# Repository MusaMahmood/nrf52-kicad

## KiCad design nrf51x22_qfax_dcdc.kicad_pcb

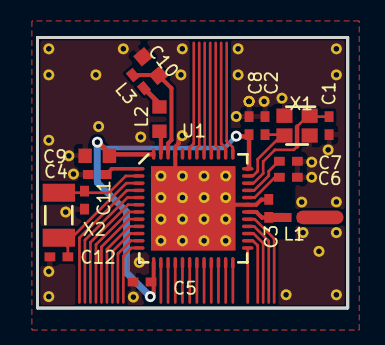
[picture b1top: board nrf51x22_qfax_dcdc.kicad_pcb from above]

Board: 2 copper layers, 17.2 x 15.0 mm, 18 parts (0 on the bottom side), 13 nets.

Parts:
C1, C2, C11, C12: 12pF; CAPC1005X04L
C3: .8pF; CAPC1005X04L
C4, C5, C8: 100nF; CAPC1005X04L
C6: NC; CAPC1005X04L
C7: 100pF; CAPC1005X04L
C9: 4.7uF; CAPC1608X06L
C10: 1.0uF; CAPC1608X06L
L1: 3.9nH; INDC1005X04L
L2: 10uH; INDC1608X06L
L3: 15nH; INDC1005X04L
U1: nrf51822-qfax; nrf51-qfax-1ep-vias
X1: Crystal-4; BT-XTAL_2016
X2: 32.768kHz; XTAL_3215

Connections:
/VDD_nRF: C5.2, C8.2, C9.2, U1.13, U1.36, U1.48
GND: C1.2, C2.2, C3.2, C4.1, C5.1, C6.1, C7.1, C8.1, C9.1, C10.1, C11.1, C12.1, U1.31, U1.45, U1.49, X1.2, X1.4
unnamed: C1.1, U1.34, X1.1
unnamed: C2.1, U1.35, X1.3
unnamed: C3.1, L1.1, U1.30
unnamed: C4.2, U1.1
unnamed: C6.2, U1.32
unnamed: C7.2, U1.33
unnamed: C10.2, L3.1, U1.46
unnamed: C11.2, U1.2, X2.2
unnamed: C12.2, U1.3, X2.1
unnamed: L2.1, L3.2
unnamed: L2.2, U1.47

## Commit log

2016-03-16 fork nrf51
2016-03-17 converted qfaa dcdc reference layout .9
2016-03-17 kicad touches and updats kicad_pcb
2016-03-17 swap for stiched vias
2016-03-17 replace components with library parts
2016-03-17 fix zones and pour
2016-03-17 cleanup
2016-03-17 schematic and netlist imported to board
2016-03-17 remove cached lib
2016-03-17 no idea
2016-03-17 add missing x1
2016-03-17 swap 3 via back to vdd, and rotate parts so nets are correct
2016-03-17 add grid origin and regen gerbers
2016-03-17 bom and library backup
